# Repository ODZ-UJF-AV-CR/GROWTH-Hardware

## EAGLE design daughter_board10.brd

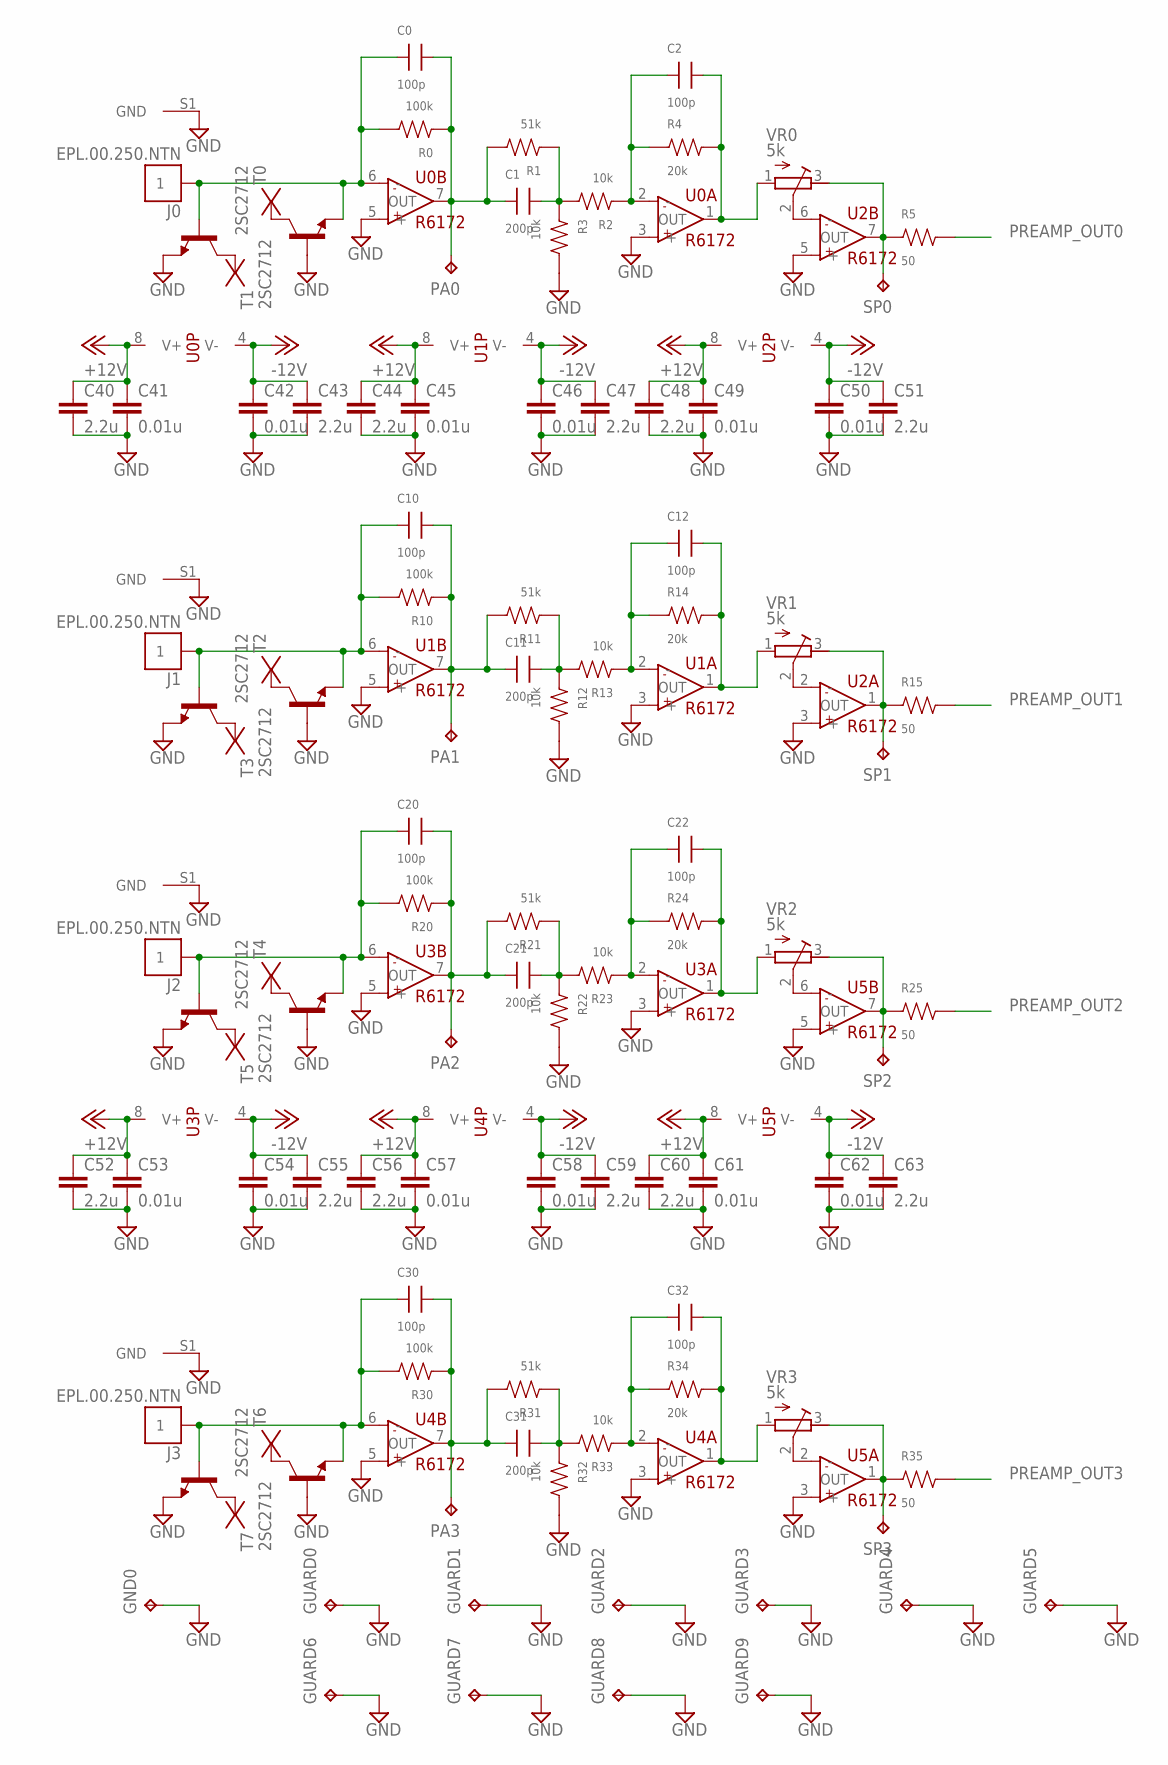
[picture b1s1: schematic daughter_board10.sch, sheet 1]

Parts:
C0, C2, C10, C12, C20, C22, C30, C32: 100p; C0603
C1, C11, C21, C31: 200p; C0603
C40, C43, C44, C47, C48, C51, C52, C55, C56, C59, C60, C63: 2.2u; C3216
C41, C42, C45, C46, C49, C50, C53, C54, C57, C58, C61, C62: 0.01u; C1608
GND0: TPPAD1-13; P1-13
GUARD0, GUARD1, GUARD2, GUARD3, GUARD4, GUARD5, GUARD6, GUARD7, GUARD8, GUARD9: TPTP17SQ; TP17SQ
J0, J1, J2, J3: EPL.00.250.NTN
PA0, PA1, PA2, PA3: TPPAD1-13; P1-13
R0, R10, R20, R30: 100k; R0603
R1, R11, R21, R31: 51k; R0603
R2, R3, R12, R13, R22, R23, R32, R33: 10k; R0603
R4, R14, R24, R34: 20k; R0603
R5, R15, R25, R35: 50; R0603
SP0, SP1, SP2, SP3: TPPAD1-13; P1-13
T0, T1, T2, T3, T4, T5, T6, T7: 2SC2712; SOT23-BEC
U0, U1, U2, U3, U4, U5: R6172; SOP8
VR0, VR1, VR2, VR3: 5k; RTRIM3296W

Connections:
+12V: C40.1, C41.1, C44.1, C45.1, C48.1, C49.1, C52.1, C53.1, C56.1, C57.1, C60.1, C61.1, U0.8 (V+), U1.8 (V+), U2.8 (V+), U3.8 (V+), U4.8 (V+), U5.8 (V+); also elsewhere on the board
-12V: C42.1, C43.1, C46.1, C47.1, C50.1, C51.1, C54.1, C55.1, C58.1, C59.1, C62.1, C63.1, U0.4 (V-), U1.4 (V-), U2.4 (V-), U3.4 (V-), U4.4 (V-), U5.4 (V-); also elsewhere on the board
GND: C40.2, C41.2, C42.2, C43.2, C44.2, C45.2, C46.2, C47.2, C48.2, C49.2, C50.2, C51.2, C52.2, C53.2, C54.2, C55.2, C56.2, C57.2, C58.2, C59.2, C60.2, C61.2, C62.2, C63.2, GND0.TP, GUARD0.TP, GUARD1.TP, GUARD2.TP, GUARD3.TP, GUARD4.TP, GUARD5.TP, GUARD6.TP, GUARD7.TP, GUARD8.TP, GUARD9.TP, J0.S1 (GND), J1.S1 (GND), J2.S1 (GND), J3.S1 (GND), R3.2, R12.2, R22.2, R32.2, T0.E, T1.B, T2.E, T3.B, T4.E, T5.B, T6.E, T7.B, U0.3 (+), U0.5 (+), U1.3 (+), U1.5 (+), U2.3 (+), U2.5 (+), U3.3 (+), U3.5 (+), U4.3 (+), U4.5 (+), U5.3 (+), U5.5 (+); also elsewhere on the board
unnamed: C0.1, J0.1, R0.2, T0.B, T1.E, U0.6 (-)
unnamed: C0.2, C1.1, PA0.TP, R0.1, R1.2, U0.7 (OUT)
unnamed: U2.6 (-), VR0.2 (S)
unnamed: C1.2, R1.1, R2.2, R3.1
unnamed: C2.1, R2.1, R4.1, U0.2 (-)
unnamed: C2.2, R4.2, U0.1 (OUT), VR0.1 (A)
unnamed: R5.1, SP0.TP, U2.7 (OUT), VR0.3 (E)
unnamed: C10.1, J1.1, R10.2, T2.B, T3.E, U1.6 (-)
unnamed: C10.2, C11.1, PA1.TP, R10.1, R11.2, U1.7 (OUT)
unnamed: C11.2, R11.1, R12.1, R13.2
unnamed: C12.1, R13.1, R14.1, U1.2 (-)
unnamed: C12.2, R14.2, U1.1 (OUT), VR1.1 (A)
unnamed: U2.2 (-), VR1.2 (S)
unnamed: R15.1, SP1.TP, U2.1 (OUT), VR1.3 (E)
unnamed: C20.2, C21.1, PA2.TP, R20.1, R21.2, U3.7 (OUT)
unnamed: C21.2, R21.1, R22.1, R23.2
unnamed: C22.1, R23.1, R24.1, U3.2 (-)
unnamed: C22.2, R24.2, U3.1 (OUT), VR2.1 (A)
unnamed: C20.1, J2.1, R20.2, T4.B, T5.E, U3.6 (-)
unnamed: U5.6 (-), VR2.2 (S)
unnamed: R25.1, SP2.TP, U5.7 (OUT), VR2.3 (E)
unnamed: C30.1, J3.1, R30.2, T6.B, T7.E, U4.6 (-)
unnamed: C30.2, C31.1, PA3.TP, R30.1, R31.2, U4.7 (OUT)
unnamed: C31.2, R31.1, R32.1, R33.2
unnamed: C32.1, R33.1, R34.1, U4.2 (-)
unnamed: C32.2, R34.2, U4.1 (OUT), VR3.1 (A)
unnamed: U5.2 (-), VR3.2 (S)
unnamed: R35.1, SP3.TP, U5.1 (OUT), VR3.3 (E)
PREAMP_OUT0: R5.2; also elsewhere on the board
PREAMP_OUT1: R15.2; also elsewhere on the board
PREAMP_OUT2: R25.2; also elsewhere on the board
PREAMP_OUT3: R35.2; also elsewhere on the board

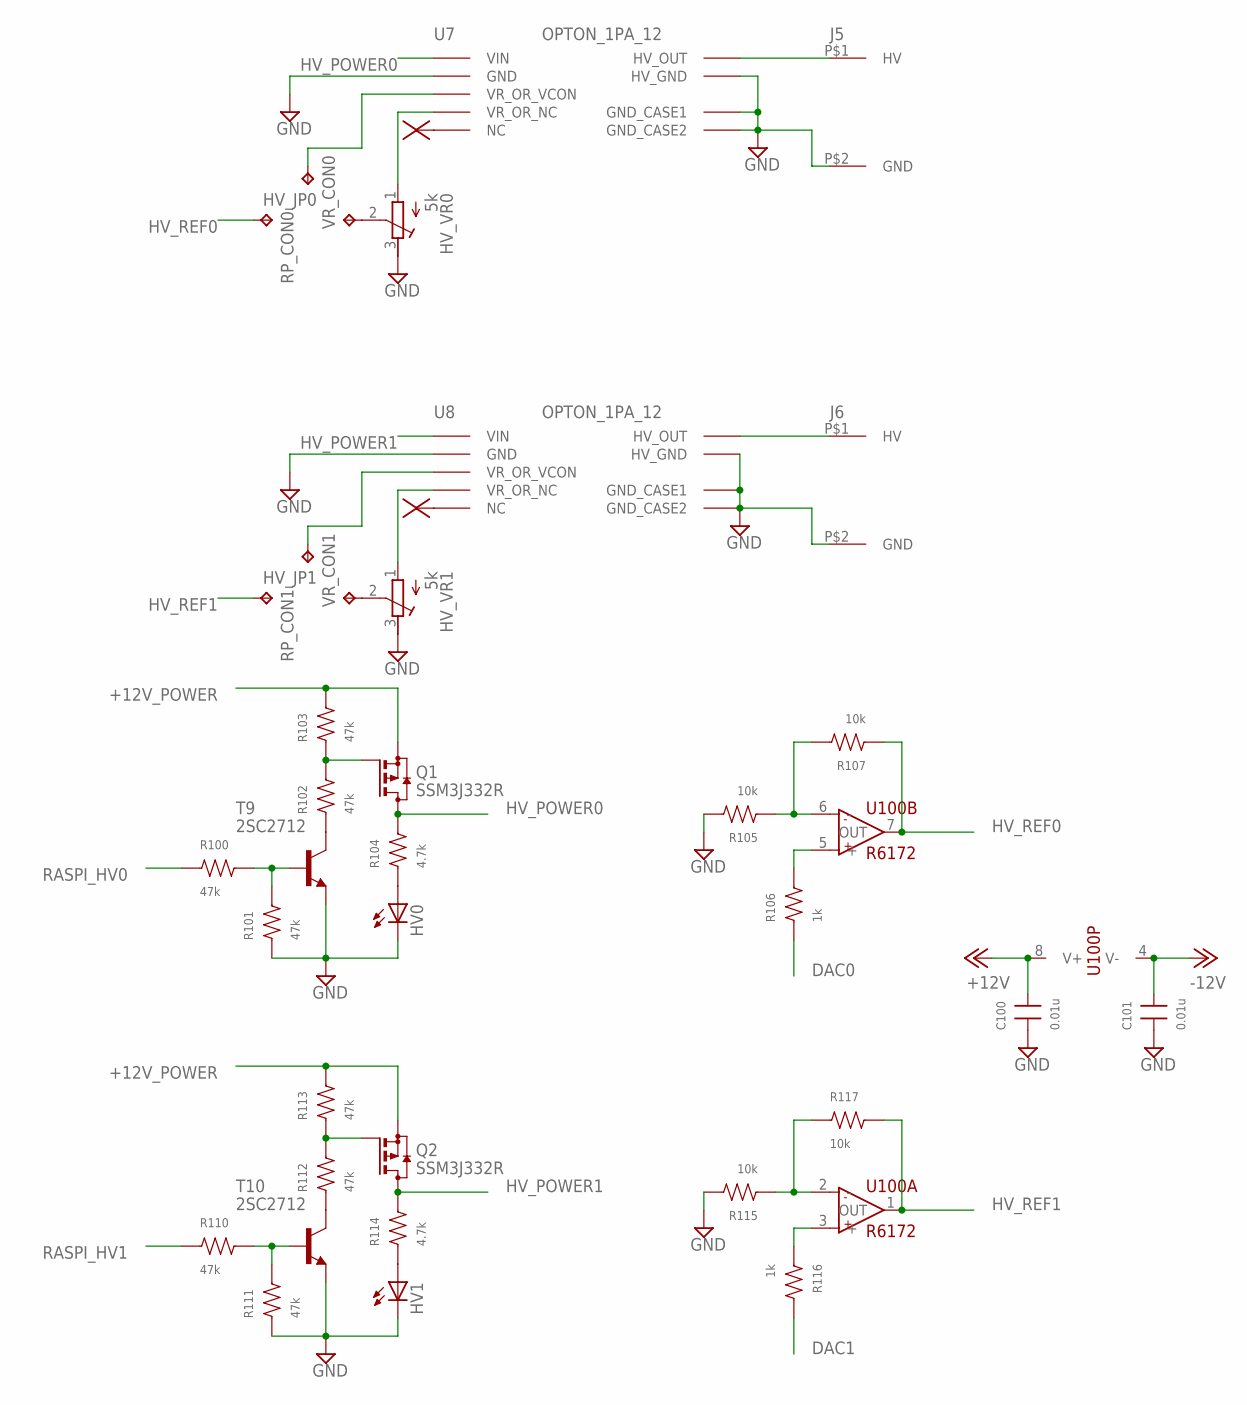
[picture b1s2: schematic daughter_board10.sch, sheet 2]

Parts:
C100, C101: 0.01u; C0603
HV0, HV1: LED_1608
HV_JP0, HV_JP1: TPPAD1-13; P1-13
HV_VR0, HV_VR1: 5k; RTRIM3296W
J5, J6: SHV_PIGTAIL_LAND
Q1, Q2: SSM3J332R; SOT23
R100, R101, R102, R103, R110, R111, R112, R113: 47k; R0603
R104, R114: 4.7k; R0603
R105, R107, R115, R117: 10k; R0603
R106, R116: 1k; R0603
RP_CON0, RP_CON1: TPPAD1-13; P1-13
T9, T10: 2SC2712; SOT23-BEC
U7, U8: OPTON_1PA_12; OPTON_PA
U100: R6172; SOP8
VR_CON0, VR_CON1: TPPAD1-13; P1-13

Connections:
+12V: C100.2, U100.8 (V+); also elsewhere on the board
+12V_POWER: Q1.2 (S), Q2.2 (S), R103.2, R113.2; also elsewhere on the board
-12V: C101.2, U100.4 (V-); also elsewhere on the board
DAC0: R106.1; also elsewhere on the board
DAC1: R116.2; also elsewhere on the board
GND: C100.1, C101.1, HV0.P$2 (C), HV1.P$2 (C), HV_VR0.3 (E), HV_VR1.3 (E), J5.P$2 (GND), J6.P$2 (GND), R101.1, R105.2, R111.1, R115.2, T9.E, T10.E, U7.P$2 (GND), U7.P$6 (HV_GND), U7.P$8 (GND_CASE1), U7.P$9 (GND_CASE2), U8.P$2 (GND), U8.P$6 (HV_GND), U8.P$8 (GND_CASE1), U8.P$9 (GND_CASE2); also elsewhere on the board
HV_POWER0: Q1.3 (D), R104.2, U7.P$1 (VIN)
HV_POWER1: Q2.3 (D), R114.2, U8.P$1 (VIN)
HV_REF0: R107.1, RP_CON0.TP, U100.7 (OUT)
HV_REF1: R117.2, RP_CON1.TP, U100.1 (OUT)
unnamed: R102.1, T9.C
unnamed: Q1.1 (G), R102.2, R103.1
unnamed: R100.2, R101.2, T9.B
unnamed: R112.1, T10.C
unnamed: Q2.1 (G), R112.2, R113.1
unnamed: HV0.P$1 (A), R104.1
unnamed: R110.2, R111.2, T10.B
unnamed: HV1.P$1 (A), R114.1
unnamed: R105.1, R107.2, U100.6 (-)
unnamed: J5.P$1 (HV), U7.P$7 (HV_OUT)
unnamed: R106.2, U100.5 (+)
unnamed: J6.P$1 (HV), U8.P$7 (HV_OUT)
unnamed: R115.1, R117.1, U100.2 (-)
unnamed: R116.1, U100.3 (+)
unnamed: HV_VR0.1 (A), U7.P$4 (VR_OR_NC)
unnamed: HV_VR1.2 (S), VR_CON1.TP
unnamed: HV_VR0.2 (S), VR_CON0.TP
unnamed: HV_VR1.1 (A), U8.P$4 (VR_OR_NC)
RASPI_HV0: R100.1; also elsewhere on the board
RASPI_HV1: R110.1; also elsewhere on the board
TP1: HV_JP0.TP, U7.P$3 (VR_OR_VCON)
TP2: HV_JP1.TP, U8.P$3 (VR_OR_VCON)

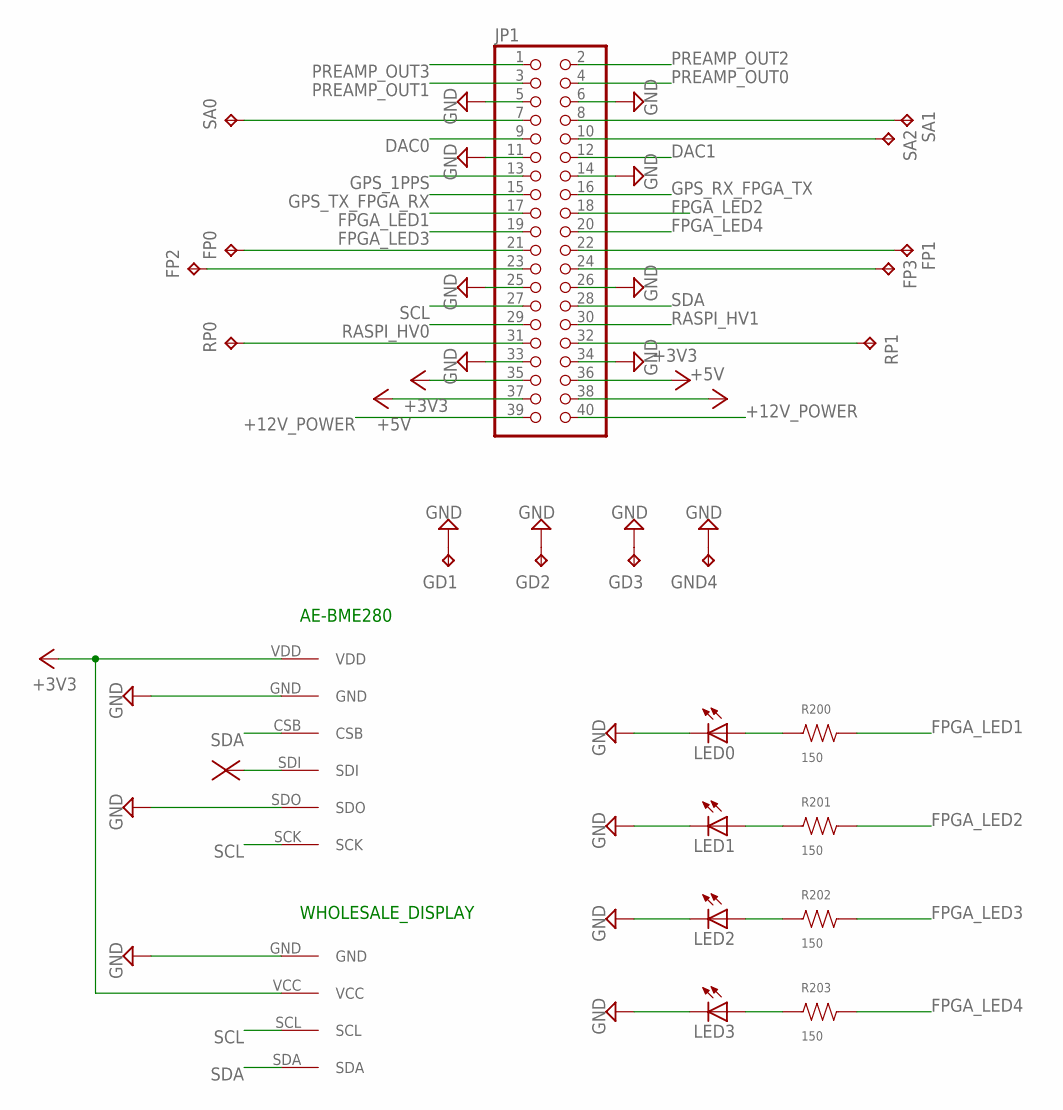
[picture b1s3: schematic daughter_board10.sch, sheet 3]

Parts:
FP0, FP1, FP2, FP3: TPPAD1-13; P1-13
GD1, GD2, GD3: TPPAD1-13; P1-13
GND4: TPPAD1-13; P1-13
JP1: PINHD-2X20; 2X20
LED0, LED1, LED2, LED3: LED_1608
R200, R201, R202, R203: 150; R0603
RP0, RP1: TPPAD1-13; P1-13
SA0, SA1, SA2: TPPAD1-13; P1-13
U$1: WHOLESALE_DISPLAY
U$2: AE-BME280

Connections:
+3V3: JP1.35, JP1.36, U$1.VCC, U$2.VDD; also elsewhere on the board
+5V: JP1.37, JP1.38
+12V_POWER: JP1.39, JP1.40; also elsewhere on the board
DAC0: JP1.9; also elsewhere on the board
DAC1: JP1.12; also elsewhere on the board
FPGA_LED1: JP1.17, R200.2
FPGA_LED2: JP1.18, R201.2
FPGA_LED3: JP1.19, R202.2
FPGA_LED4: JP1.20, R203.2
GND: GD1.TP, GD2.TP, GD3.TP, GND4.TP, JP1.5, JP1.6, JP1.11, JP1.14, JP1.25, JP1.26, JP1.33, JP1.34, LED0.P$2 (C), LED1.P$2 (C), LED2.P$2 (C), LED3.P$2 (C), U$1.GND, U$2.GND, U$2.SDO; also elsewhere on the board
GPS_1PPS: JP1.13; also elsewhere on the board
GPS_RX_FPGA_TX: JP1.16; also elsewhere on the board
GPS_TX_FPGA_RX: JP1.15; also elsewhere on the board
LED0: LED0.P$1 (A), R200.1
unnamed: JP1.31, RP0.TP
unnamed: FP2.TP, JP1.23
unnamed: FP0.TP, JP1.21
unnamed: JP1.7, SA0.TP
unnamed: JP1.8, SA1.TP
unnamed: JP1.10, SA2.TP
unnamed: FP1.TP, JP1.22
unnamed: FP3.TP, JP1.24
unnamed: LED3.P$1 (A), R203.1
unnamed: LED2.P$1 (A), R202.1
unnamed: LED1.P$1 (A), R201.1
unnamed: JP1.32, RP1.TP
PREAMP_OUT0: JP1.4; also elsewhere on the board
PREAMP_OUT1: JP1.3; also elsewhere on the board
PREAMP_OUT2: JP1.2; also elsewhere on the board
PREAMP_OUT3: JP1.1; also elsewhere on the board
RASPI_HV0: JP1.29; also elsewhere on the board
RASPI_HV1: JP1.30; also elsewhere on the board
SCL: JP1.27, U$1.SCL, U$2.SCK
SDA: JP1.28, U$1.SDA, U$2.CSB

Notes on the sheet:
AE-BME280
WHOLESALE_DISPLAY

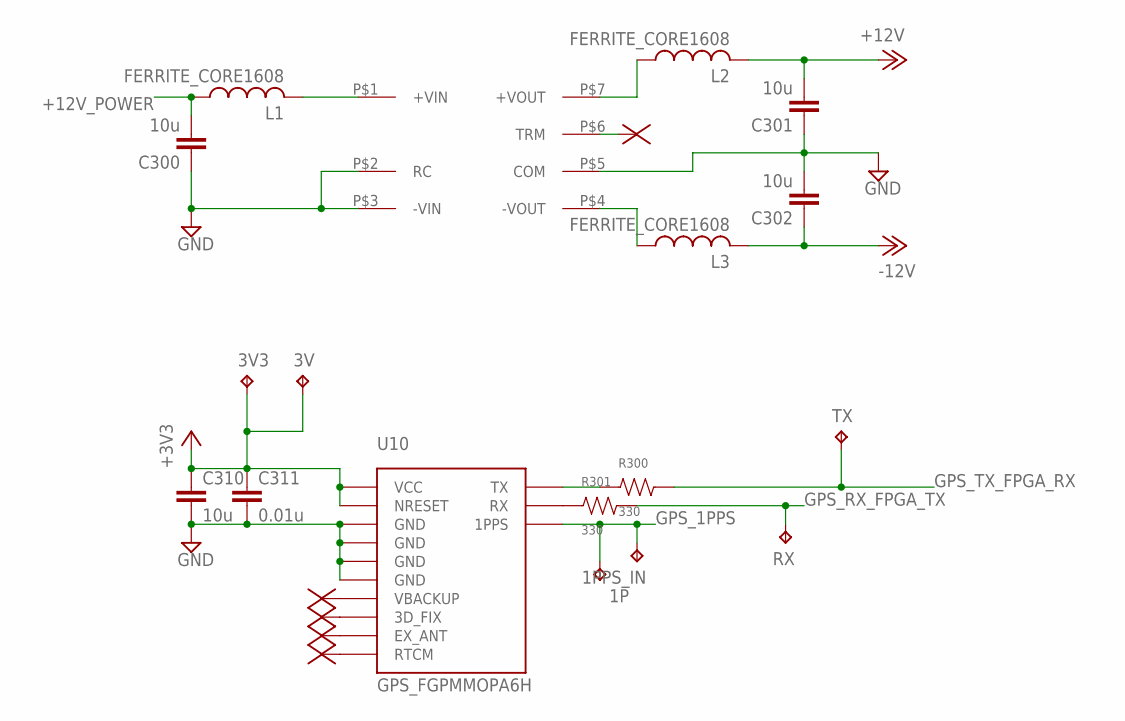
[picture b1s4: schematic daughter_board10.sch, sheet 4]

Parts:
1P, 1PPS_IN, 3V, 3V3: TPPAD1-13; P1-13
C300, C301, C302, C310: 10u; C3216
C311: 0.01u; C1608
L1, L2, L3: FERRITE_CORE1608; R0603
R300, R301: 330; R0603
RX: TPPAD1-13; P1-13
TX: TPPAD1-13; P1-13
U10: GPS_FGPMMOPA6H
U$4: CC6-SERIES

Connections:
+3V3: 3V.TP, 3V3.TP, C310.1, C311.1, U10.P$1 (VCC), U10.P$2 (NRESET); also elsewhere on the board
+12V: C301.2, L2.2; also elsewhere on the board
+12V_POWER: C300.2, L1.1; also elsewhere on the board
-12V: C302.1, L3.2; also elsewhere on the board
GND: C300.1, C301.1, C302.2, C310.2, C311.2, U10.P$3 (GND), U10.P$8 (GND), U10.P$12 (GND), U10.P$19 (GND), U$4.P$2 (RC), U$4.P$3 (-VIN), U$4.P$5 (COM); also elsewhere on the board
GPS_1PPS: 1P.TP, 1PPS_IN.TP, U10.P$13 (1PPS); also elsewhere on the board
GPS_RX_FPGA_TX: R301.2, RX.TP; also elsewhere on the board
GPS_TX_FPGA_RX: R300.2, TX.TP; also elsewhere on the board
unnamed: L2.1, U$4.P$7 (+VOUT)
unnamed: L3.1, U$4.P$4 (-VOUT)
unnamed: L1.2, U$4.P$1 (+VIN)
unnamed: R301.1, U10.P$10 (RX)
unnamed: R300.1, U10.P$9 (TX)

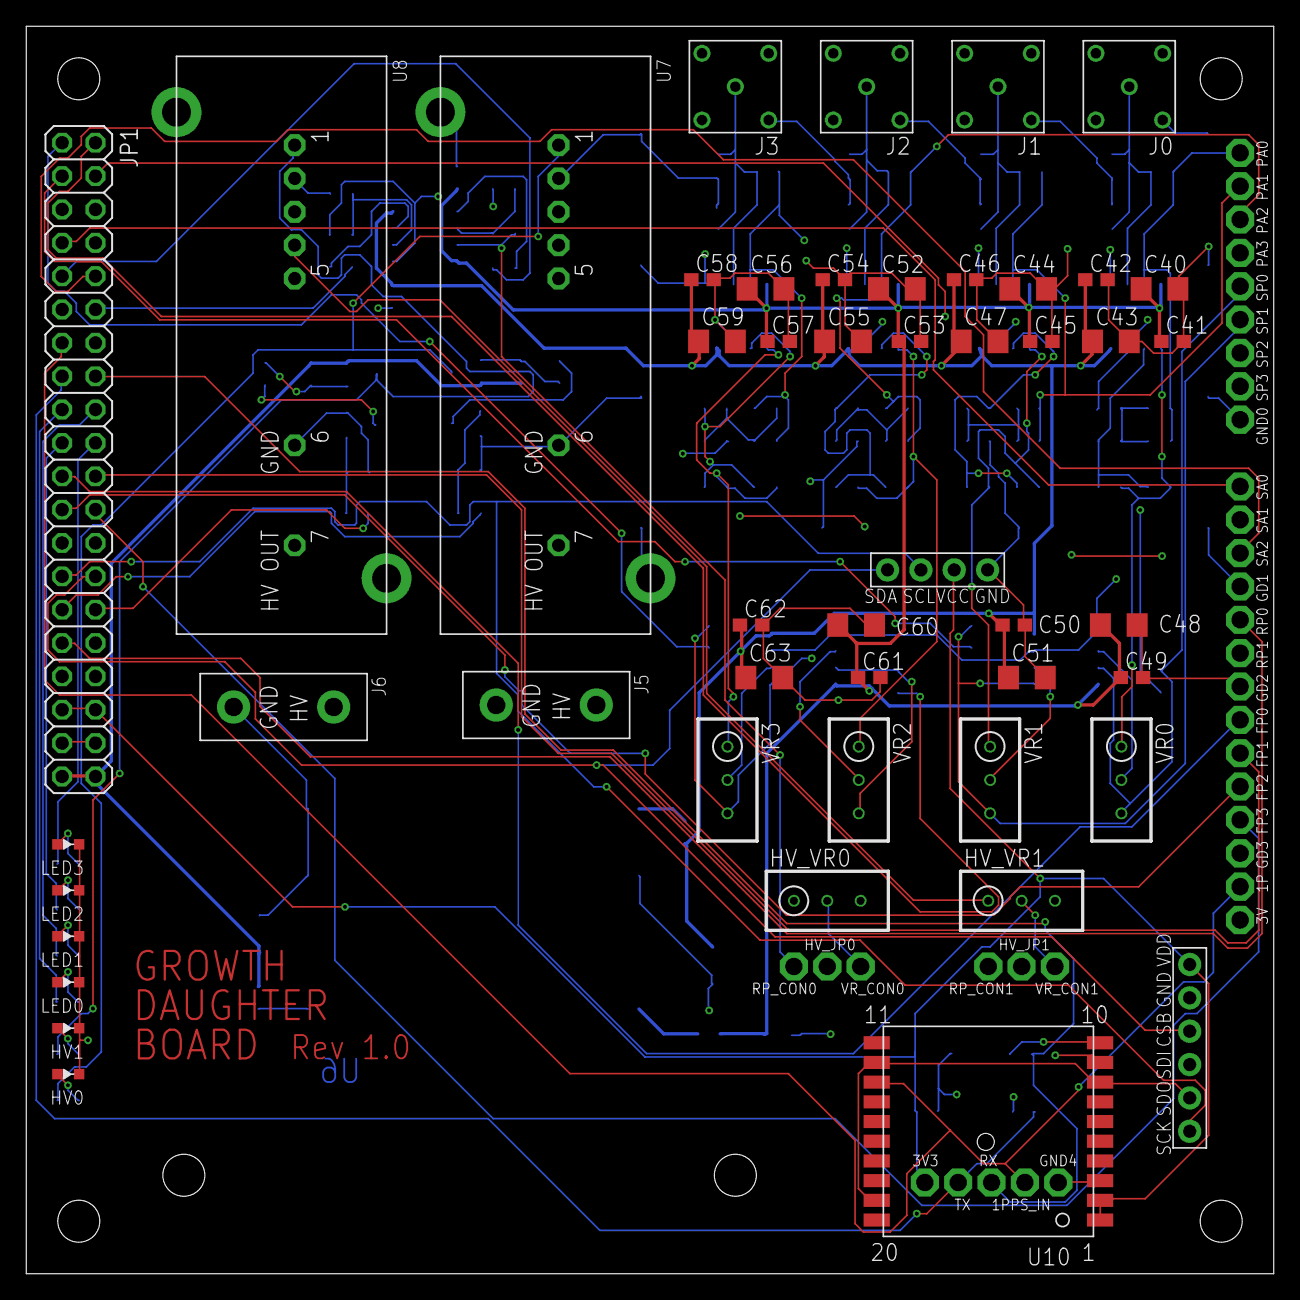
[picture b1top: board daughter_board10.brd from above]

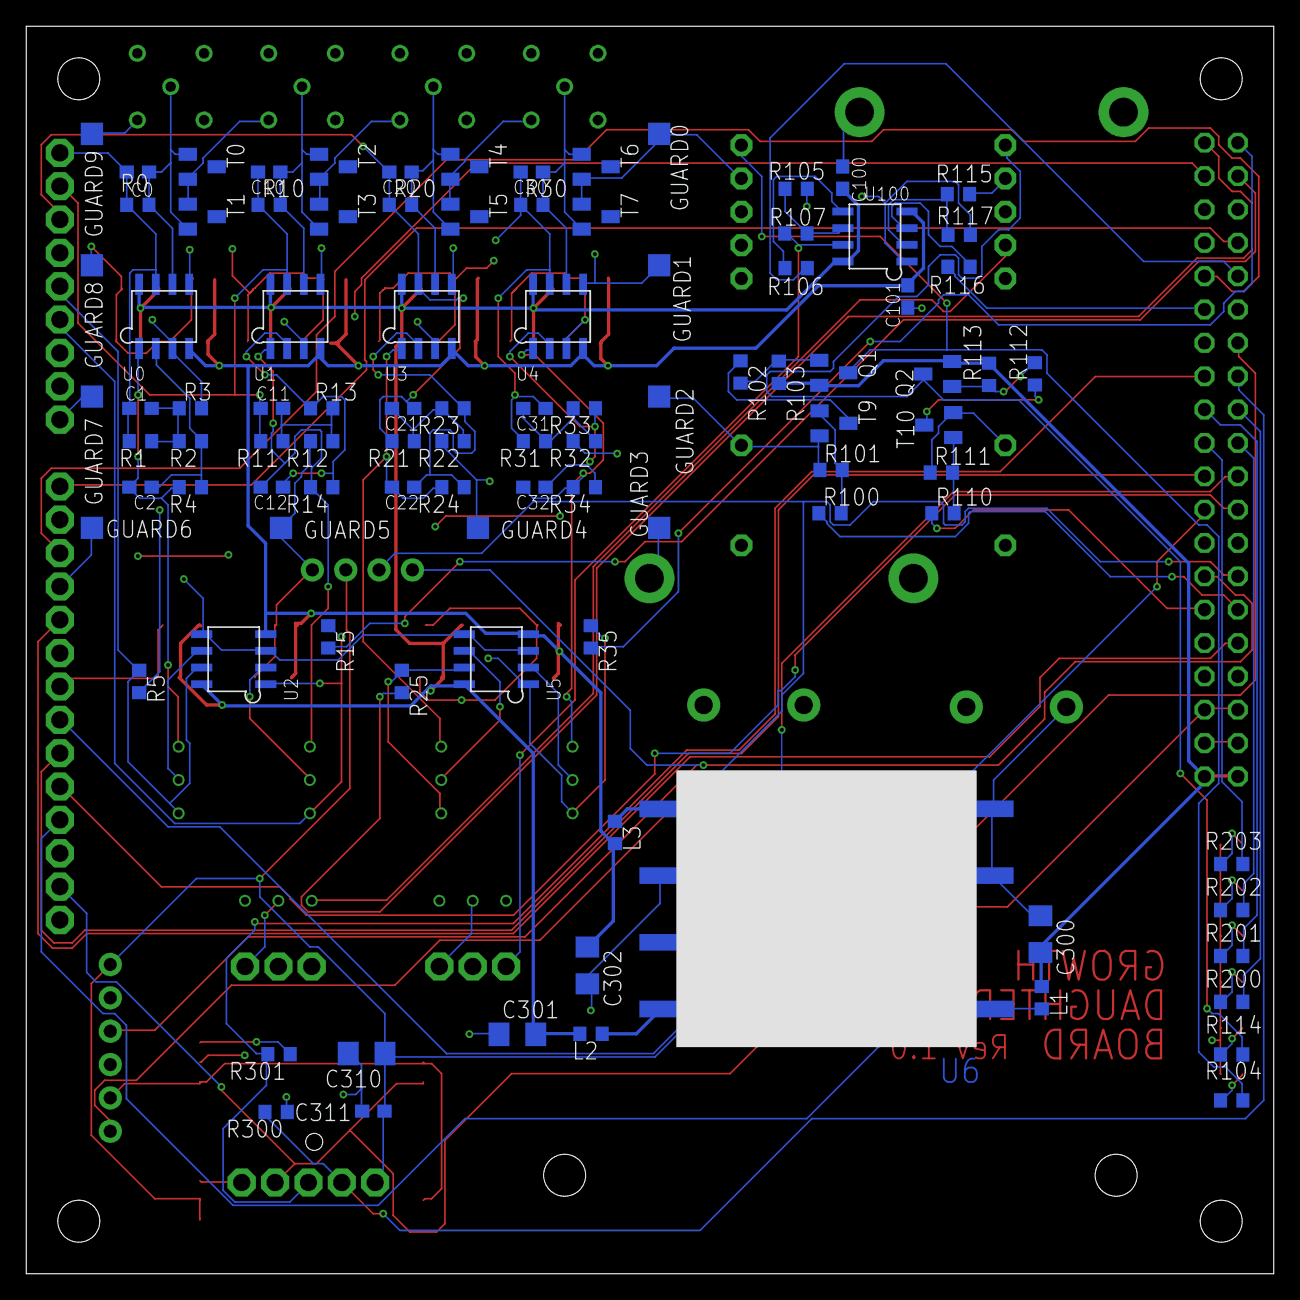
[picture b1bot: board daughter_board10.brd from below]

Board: 4 copper layers, 95.0 x 95.0 mm, 180 parts (98 on the bottom side), 93 nets.

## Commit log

2016-08-15 add eagle files
